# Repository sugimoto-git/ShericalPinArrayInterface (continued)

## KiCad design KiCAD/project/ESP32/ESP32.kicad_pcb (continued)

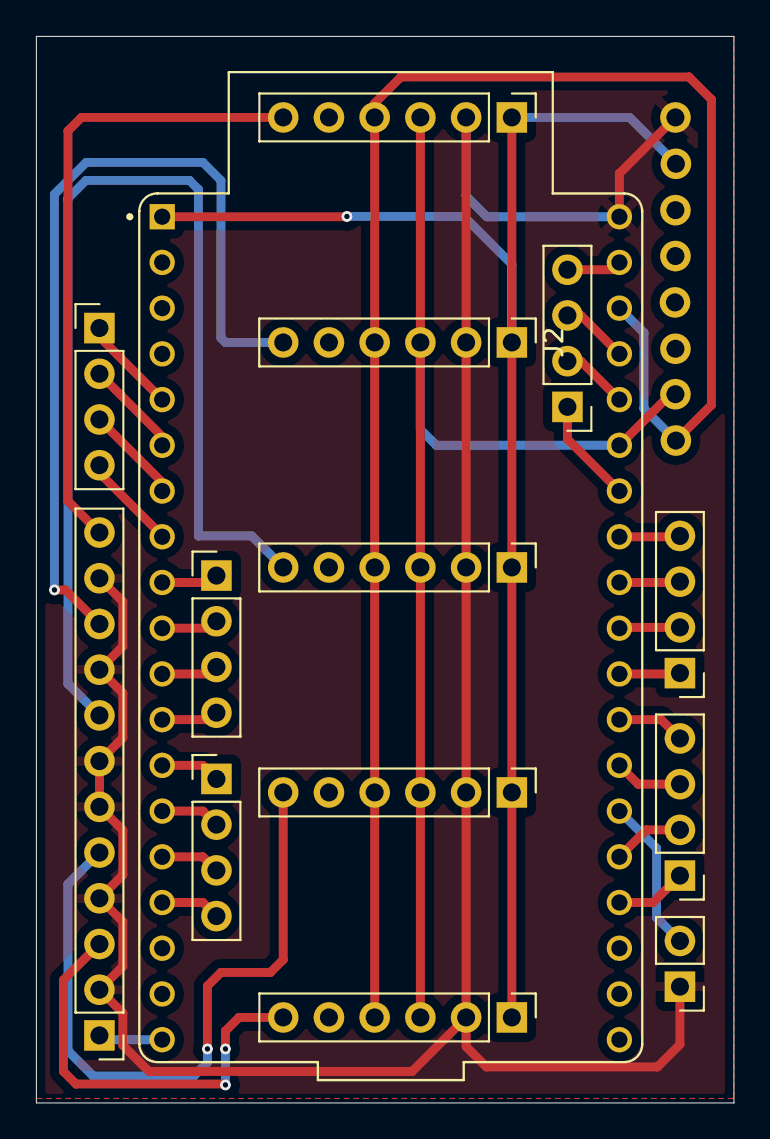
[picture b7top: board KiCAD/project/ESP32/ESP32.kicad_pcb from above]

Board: 2 copper layers, 38.8 x 59.2 mm, 15 parts (1 on the bottom side), 35 nets.

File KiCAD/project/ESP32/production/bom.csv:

Designator,Footprint,Quantity,Value,LCSC Part #
"J1, J2, J3, J4, J5",PinHeader_1x06_P2.54mm_Vertical,5,Conn_01x06_Pin,
"J13, J14, J15, J16, J6, J8",PinHeader_1x04_P2.54mm_Vertical,6,Conn_01x04_Pin,
J7,PinHeader_1x12_P2.54mm_Vertical,1,Conn_01x12_Pin,
J9,PinHeader_1x02_P2.54mm_Vertical,1,Conn_01x02_Pin,
U1,MODULE_ESP32-DEVKITC-32E,1,ESP32-DEVKITC-32E,
U2,ADXL345,1,~,

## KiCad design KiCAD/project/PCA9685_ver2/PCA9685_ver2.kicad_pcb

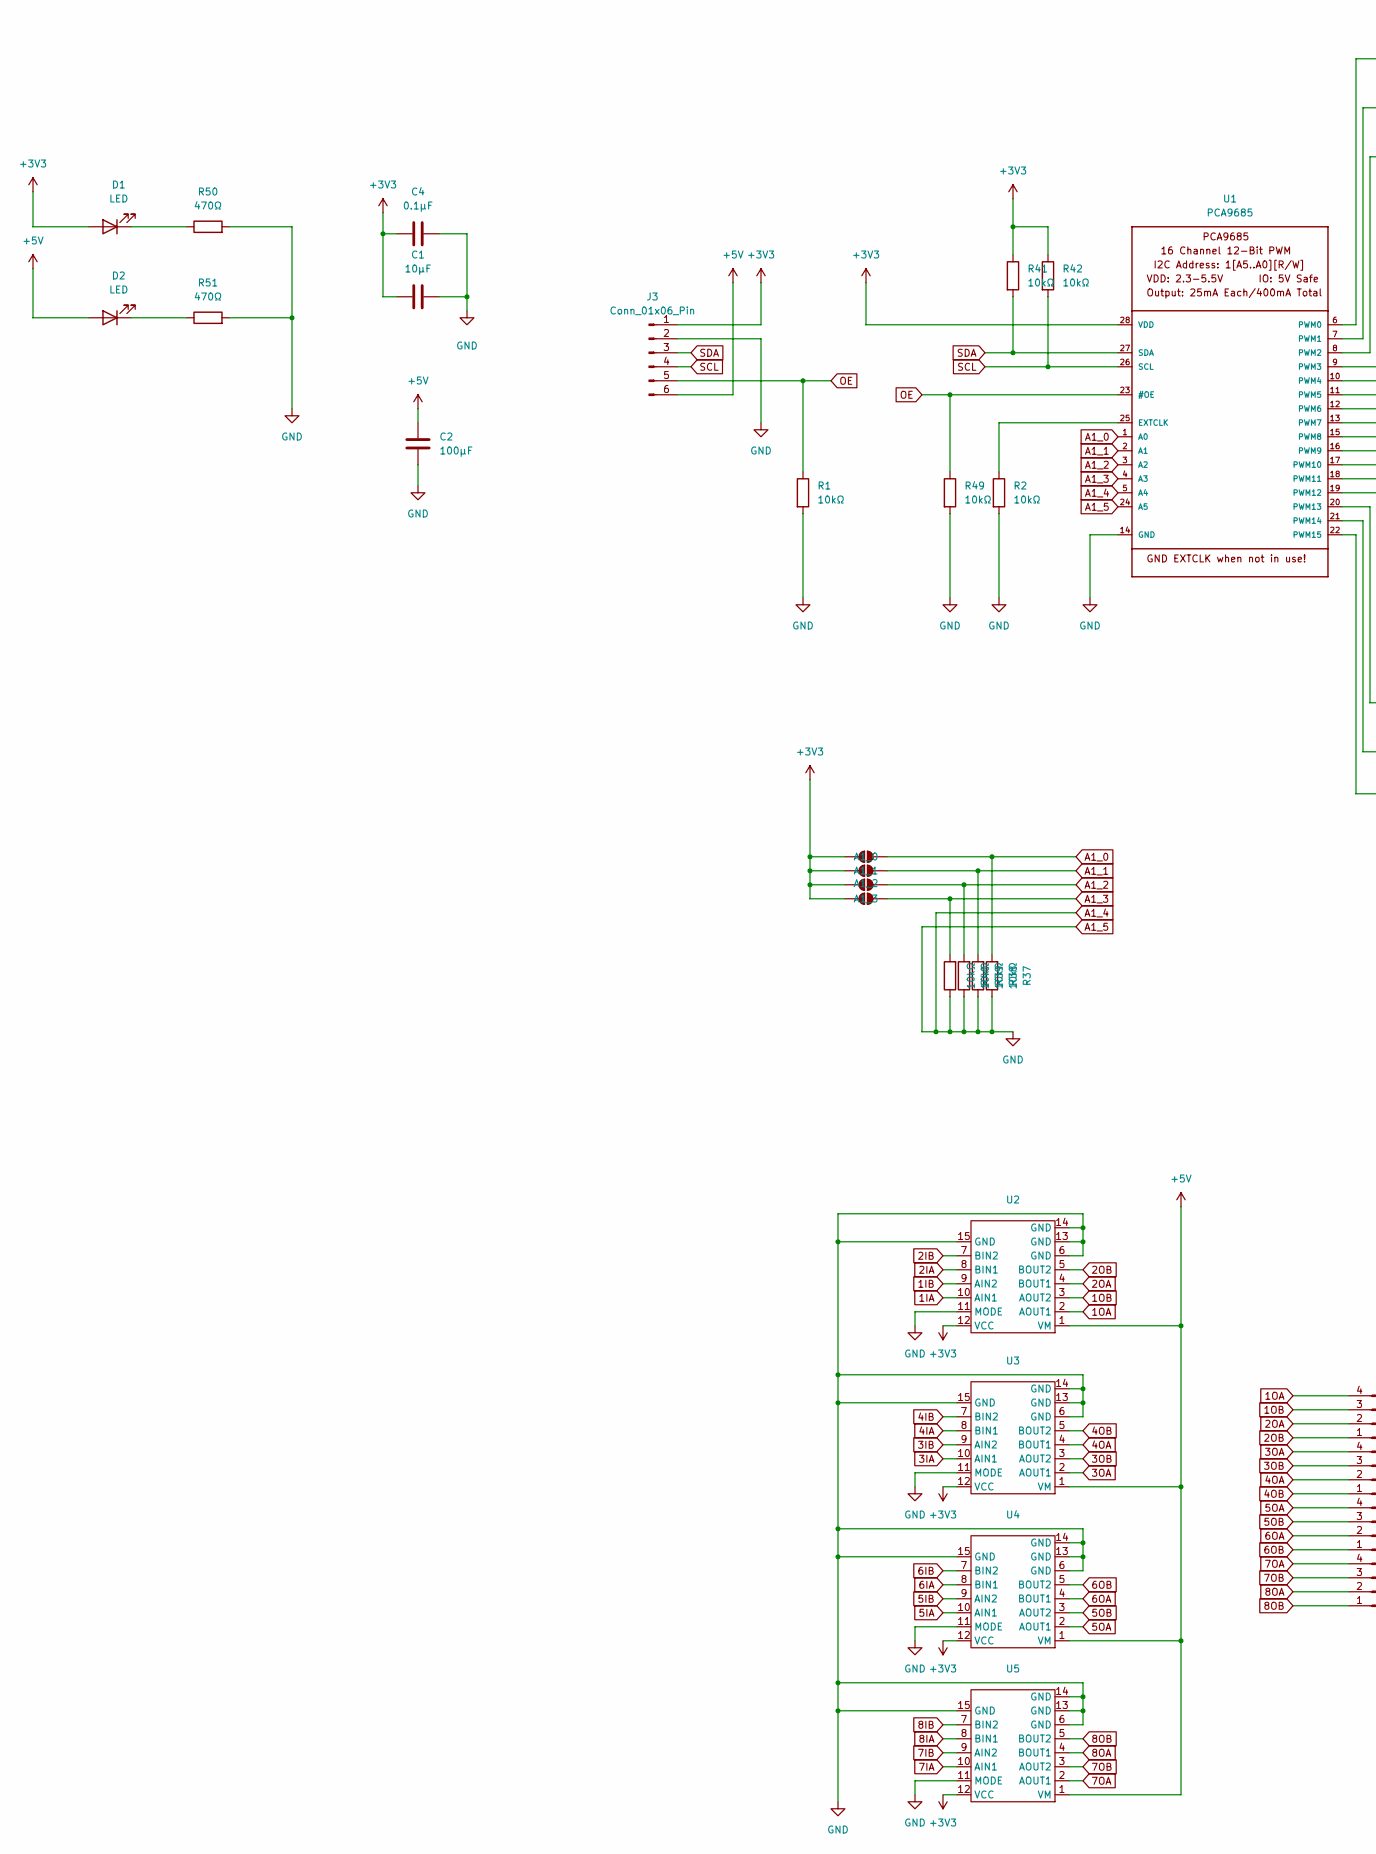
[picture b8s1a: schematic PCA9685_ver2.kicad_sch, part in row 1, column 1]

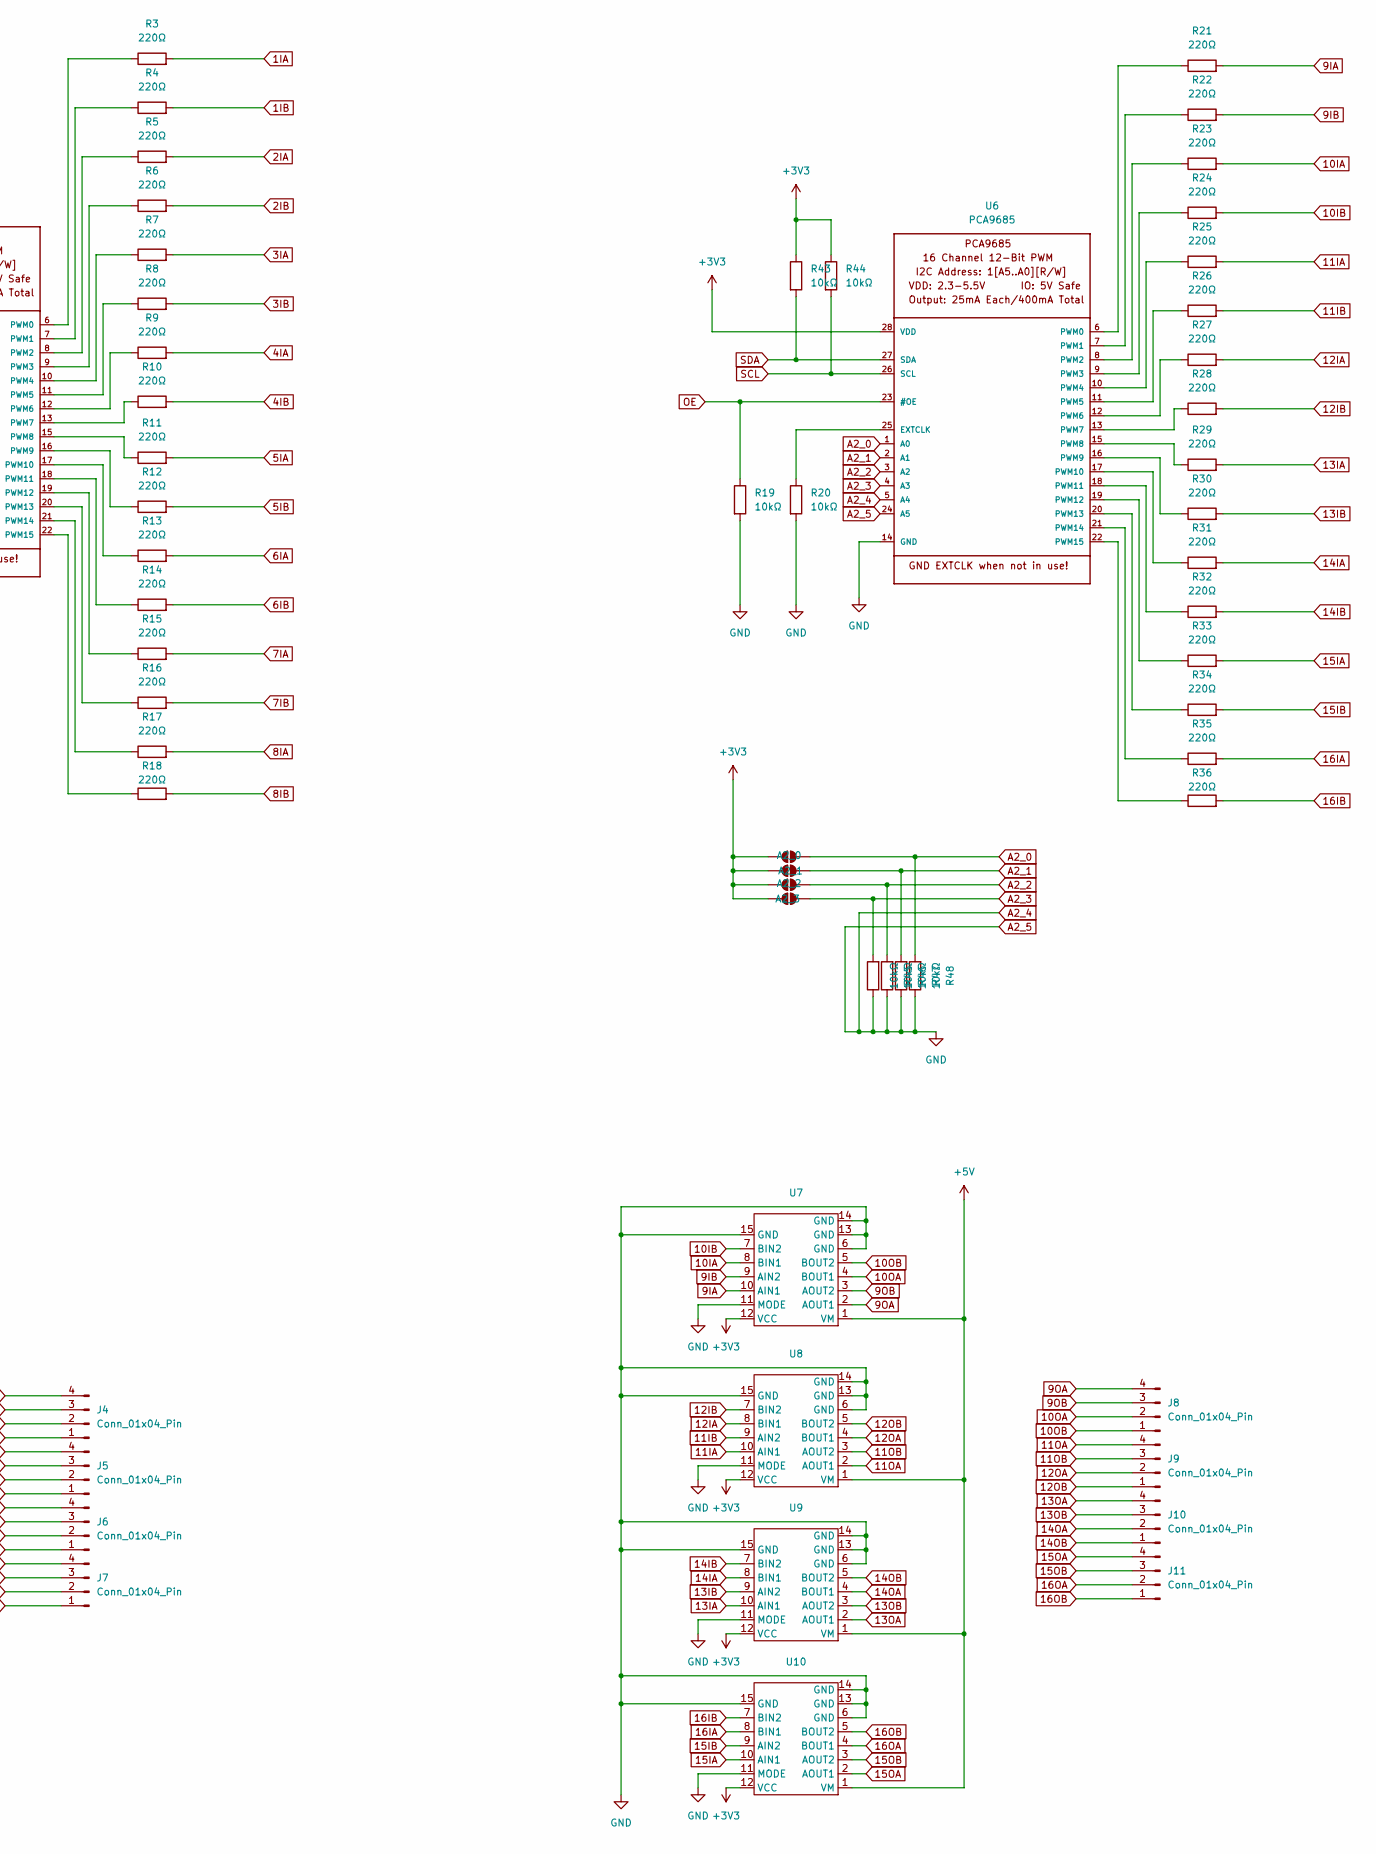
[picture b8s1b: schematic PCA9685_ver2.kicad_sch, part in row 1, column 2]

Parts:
A1_0, A1_1, A1_2, A1_3, A2_0, A2_1, A2_2, A2_3: SolderJumper_2_Open; SolderJumper-2_P1.3mm_Open_RoundedPad1.0x1.5mm
C1: 10μF; C_0603_1608Metric
C2: 100μF; C_1206_3216Metric
C4: 0.1μF; C_0603_1608Metric
D1, D2: LED; CP_EIA-3528-12_Kemet-T
J3: Conn_01x06_Pin; PinHeader_1x06_P2.54mm_Horizontal
J4, J5, J6, J7, J8, J9, J10, J11: Conn_01x04_Pin; PinHeader_1x04_P2.54mm_Horizontal
R1, R2, R19, R20, R37, R38, R39, R40, R41, R42, R43, R44, R45, R46, R47, R48, R49: 10kΩ; R_0402_1005Metric
R3, R4, R5, R6, R7, R8, R9, R10, R11, R12, R13, R14, R15, R16, R17, R18, R21, R22, R23, R24, R25, R26, R27, R28, R29, R30, R31, R32, R33, R34, R35, R36: 220Ω; R_0201_0603Metric
R50, R51: 470Ω; R_0402_1005Metric
U1, U6: PCA9685; TSSOP-28_4.4x9.7mm_P0.65mm
U2, U3, U4, U5, U7, U8, U9, U10: SON50P300X200X80-13N

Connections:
1IA: R3.2, U2.10 (AIN1)
1IB: R4.2, U2.9 (AIN2)
1OA: J4.4, U2.2 (AOUT1)
1OB: J4.3, U2.3 (AOUT2)
2IA: R5.2, U2.8 (BIN1)
2IB: R6.2, U2.7 (BIN2)
2OA: J4.2, U2.4 (BOUT1)
2OB: J4.1, U2.5 (BOUT2)
3IA: R7.2, U3.10 (AIN1)
3IB: R8.2, U3.9 (AIN2)
3OA: J5.4, U3.2 (AOUT1)
3OB: J5.3, U3.3 (AOUT2)
4IA: R9.2, U3.8 (BIN1)
4IB: R10.2, U3.7 (BIN2)
4OA: J5.2, U3.4 (BOUT1)
4OB: J5.1, U3.5 (BOUT2)
5IA: R11.2, U4.10 (AIN1)
5IB: R12.2, U4.9 (AIN2)
5OA: J6.4, U4.2 (AOUT1)
5OB: J6.3, U4.3 (AOUT2)
6IA: R13.2, U4.8 (BIN1)
6IB: R14.2, U4.7 (BIN2)
6OA: J6.2, U4.4 (BOUT1)
6OB: J6.1, U4.5 (BOUT2)
7IA: R15.2, U5.10 (AIN1)
7IB: R16.2, U5.9 (AIN2)
7OA: J7.4, U5.2 (AOUT1)
7OB: J7.3, U5.3 (AOUT2)
8IA: R17.2, U5.8 (BIN1)
8IB: R18.2, U5.7 (BIN2)
8OA: J7.2, U5.4 (BOUT1)
8OB: J7.1, U5.5 (BOUT2)
9IA: R21.2, U7.10 (AIN1)
9IB: R22.2, U7.9 (AIN2)
9OA: J8.4, U7.2 (AOUT1)
9OB: J8.3, U7.3 (AOUT2)
10IA: R23.2, U7.8 (BIN1)
10IB: R24.2, U7.7 (BIN2)
10OA: J8.2, U7.4 (BOUT1)
10OB: J8.1, U7.5 (BOUT2)
11IA: R25.2, U8.10 (AIN1)
11IB: R26.2, U8.9 (AIN2)
11OA: J9.4, U8.2 (AOUT1)
11OB: J9.3, U8.3 (AOUT2)
12IA: R27.2, U8.8 (BIN1)
12IB: R28.2, U8.7 (BIN2)
12OA: J9.2, U8.4 (BOUT1)
12OB: J9.1, U8.5 (BOUT2)
13IA: R29.2, U9.10 (AIN1)
13IB: R30.2, U9.9 (AIN2)
13OA: J10.4, U9.2 (AOUT1)
13OB: J10.3, U9.3 (AOUT2)
14IA: R31.2, U9.8 (BIN1)
14IB: R32.2, U9.7 (BIN2)
14OA: J10.2, U9.4 (BOUT1)
14OB: J10.1, U9.5 (BOUT2)
15IA: R33.2, U10.10 (AIN1)
15IB: R34.2, U10.9 (AIN2)
15OA: J11.4, U10.2 (AOUT1)
15OB: J11.3, U10.3 (AOUT2)
16IA: R35.2, U10.8 (BIN1)
16IB: R36.2, U10.7 (BIN2)
16OA: J11.2, U10.4 (BOUT1)
16OB: J11.1, U10.5 (BOUT2)
+3V3: A1_0.1 (A), A1_1.1 (A), A1_2.1 (A), A1_3.1 (A), A2_0.1 (A), A2_1.1 (A), A2_2.1 (A), A2_3.1 (A), C1.1, C4.2, D1.2 (A), J3.1, R41.1, R42.1, R43.1, R44.1, U1.28 (VDD), U2.12 (VCC), U3.12 (VCC), U4.12 (VCC), U5.12 (VCC), U6.28 (VDD), U7.12 (VCC), U8.12 (VCC), U9.12 (VCC), U10.12 (VCC)
+5V: C2.1, D2.2 (A), J3.6, U2.1 (VM), U3.1 (VM), U4.1 (VM), U5.1 (VM), U7.1 (VM), U8.1 (VM), U9.1 (VM), U10.1 (VM)
A1_0: A1_0.2 (B), R37.2, U1.1 (A0)
A1_1: A1_1.2 (B), R38.2, U1.2 (A1)
A1_2: A1_2.2 (B), R39.2, U1.3 (A2)
A1_3: A1_3.2 (B), R40.2, U1.4 (A3)
A1_4: C1.2, C2.2, C4.1, J3.2, R1.2, R2.2, R19.2, R20.2, R37.1, R38.1, R39.1, R40.1, R45.1, R46.1, R47.1, R48.1, R49.2, R50.2, R51.2, U1.5 (A4), U1.14 (GND), U1.24 (A5), U2.6 (GND), U2.11 (MODE), U2.13 (GND), U2.14 (GND), U2.15 (GND), U3.6 (GND), U3.11 (MODE), U3.13 (GND), U3.14 (GND), U3.15 (GND), U4.6 (GND), U4.11 (MODE), U4.13 (GND), U4.14 (GND), U4.15 (GND), U5.6 (GND), U5.11 (MODE), U5.13 (GND), U5.14 (GND), U5.15 (GND), U6.5 (A4), U6.14 (GND), U6.24 (A5), U7.6 (GND), U7.11 (MODE), U7.13 (GND), U7.14 (GND), U7.15 (GND), U8.6 (GND), U8.11 (MODE), U8.13 (GND), U8.14 (GND), U8.15 (GND), U9.6 (GND), U9.11 (MODE), U9.13 (GND), U9.14 (GND), U9.15 (GND), U10.6 (GND), U10.11 (MODE), U10.13 (GND), U10.14 (GND), U10.15 (GND)
A2_0: A2_0.2 (B), R48.2, U6.1 (A0)
A2_1: A2_1.2 (B), R47.2, U6.2 (A1)
A2_2: A2_2.2 (B), R46.2, U6.3 (A2)
A2_3: A2_3.2 (B), R45.2, U6.4 (A3)
unnamed: D1.1 (K), R50.1
unnamed: D2.1 (K), R51.1
unnamed: R2.1, U1.25 (EXTCLK)
unnamed: R3.1, U1.6 (PWM0)
unnamed: R4.1, U1.7 (PWM1)
unnamed: R5.1, U1.8 (PWM2)
unnamed: R6.1, U1.9 (PWM3)
unnamed: R7.1, U1.10 (PWM4)
unnamed: R8.1, U1.11 (PWM5)
unnamed: R9.1, U1.12 (PWM6)
unnamed: R10.1, U1.13 (PWM7)
unnamed: R11.1, U1.15 (PWM8)
unnamed: R12.1, U1.16 (PWM9)
unnamed: R13.1, U1.17 (PWM10)
unnamed: R14.1, U1.18 (PWM11)
unnamed: R15.1, U1.19 (PWM12)
unnamed: R16.1, U1.20 (PWM13)
unnamed: R17.1, U1.21 (PWM14)
unnamed: R18.1, U1.22 (PWM15)
unnamed: R20.1, U6.25 (EXTCLK)
unnamed: R21.1, U6.6 (PWM0)
unnamed: R22.1, U6.7 (PWM1)
unnamed: R23.1, U6.8 (PWM2)
unnamed: R24.1, U6.9 (PWM3)
unnamed: R25.1, U6.10 (PWM4)
unnamed: R26.1, U6.11 (PWM5)
unnamed: R27.1, U6.12 (PWM6)
unnamed: R28.1, U6.13 (PWM7)
unnamed: R29.1, U6.15 (PWM8)
unnamed: R30.1, U6.16 (PWM9)
unnamed: R31.1, U6.17 (PWM10)
unnamed: R32.1, U6.18 (PWM11)
unnamed: R33.1, U6.19 (PWM12)
unnamed: R34.1, U6.20 (PWM13)
unnamed: R35.1, U6.21 (PWM14)
unnamed: R36.1, U6.22 (PWM15)
OE: J3.5, R1.1, R19.1, R49.1, U1.23 (#OE), U6.23 (#OE)
SCL: J3.4, R42.2, R44.2, U1.26 (SCL), U6.26 (SCL)
SDA: J3.3, R41.2, R43.2, U1.27 (SDA), U6.27 (SDA)

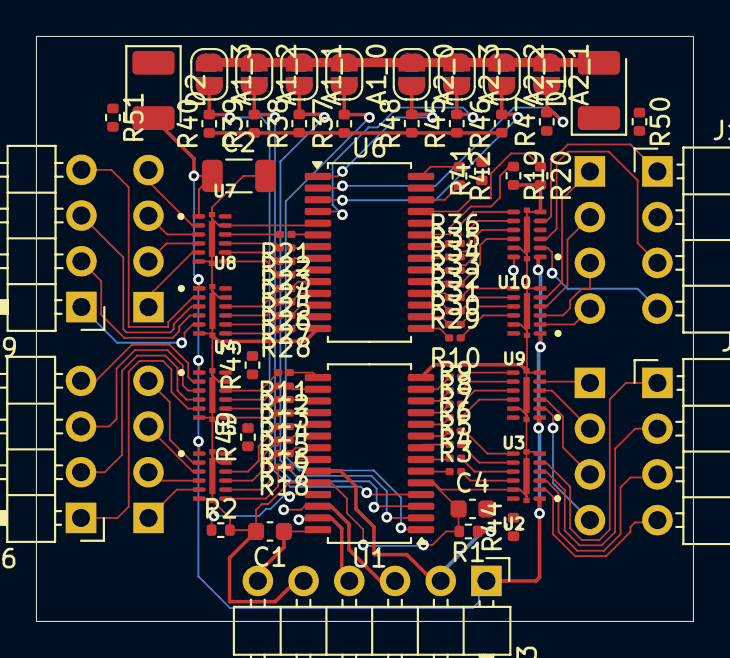
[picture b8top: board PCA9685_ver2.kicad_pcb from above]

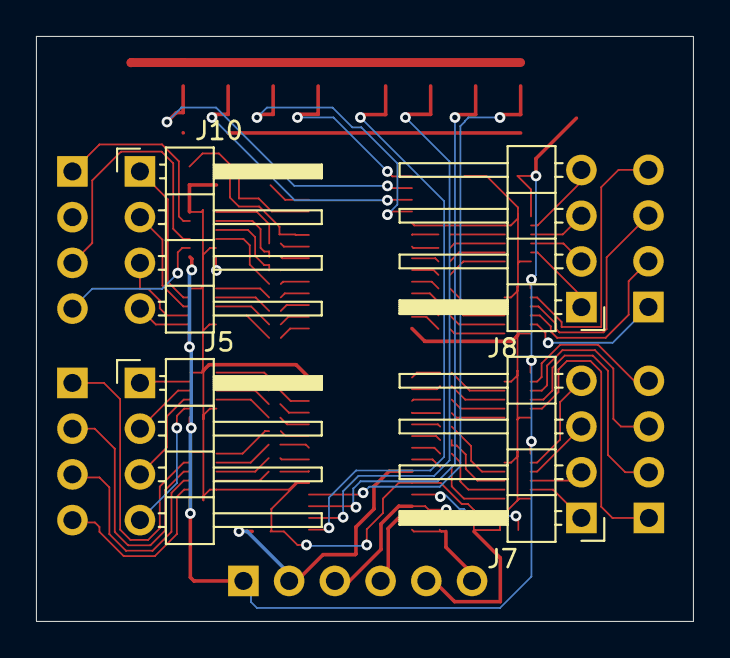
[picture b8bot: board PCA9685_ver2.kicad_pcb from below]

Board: 2 copper layers, 36.5 x 32.5 mm, 83 parts (4 on the bottom side), 114 nets.

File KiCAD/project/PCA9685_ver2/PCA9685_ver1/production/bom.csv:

Designator,Footprint,Quantity,Value,LCSC Part #
"C1, C3",0603,2,10μF,
C2,0805,1,47μF,
"J1, J6, J7, J8",PinHeader_1x04_P2.54mm_Vertical,4,Conn_01x04_Pin,
"J2, J3",PinHeader_1x06_P2.54mm_Vertical,2,Conn_01x06_Pin,
J4,Molex_KK-254_AE-6410-02A_1x02_P2.54mm_Vertical,1,Conn_01x02,
"R1, R19, R2, R20, R21, R22, R23, R24",0402,8,10kΩ,
"R10, R11, R12, R13, R14, R15, R16, R17, R18, R3, R4, R5, R6, R7, R8, R9",0402,16,220Ω,
"R25, R26",0805,2,4.7kΩ,
U1,TSSOP-28_4.4x9.7mm_P0.65mm,1,PCA9685,

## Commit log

2024-12-09 KiCAD and Arduino data
2024-12-16 git clone https://sugimoto-git: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@github.com/sugimoto-git/ShericalPinArrayInterface.git
    python data
2024-12-16 paper upload
2024-12-16 paper update
2024-12-16 pptx remove
